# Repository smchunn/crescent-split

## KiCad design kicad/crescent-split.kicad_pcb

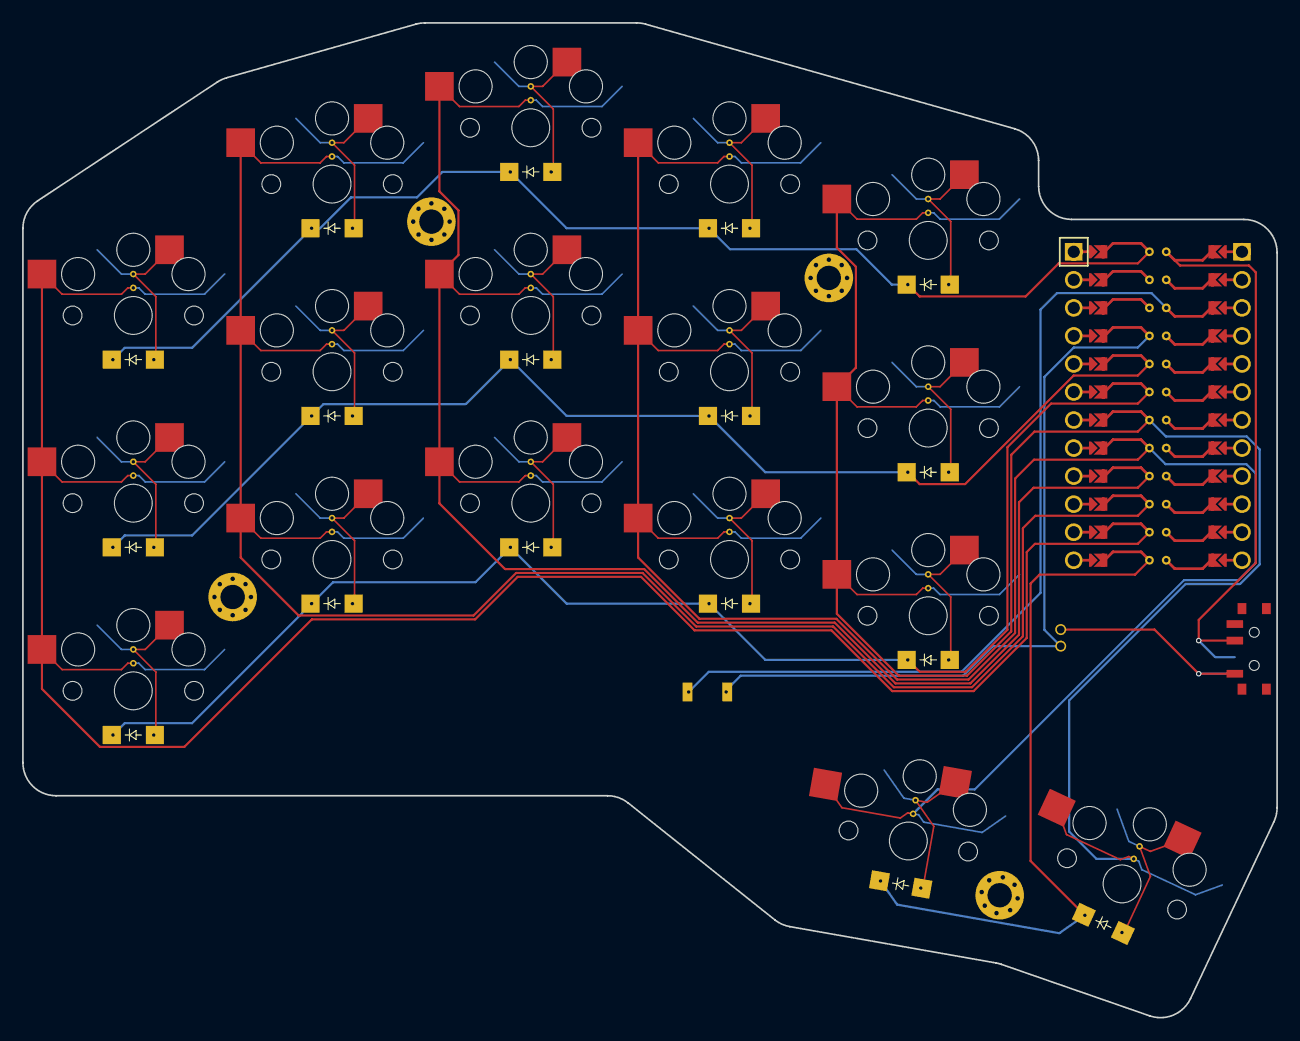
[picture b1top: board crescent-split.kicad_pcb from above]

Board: 2 copper layers, 113.6 x 90.1 mm, 39 parts (0 on the bottom side), 27 nets.

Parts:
D1, D2, D3, D4, D5, D6, D7, D8, D9, D10, D11, D12, D13, D14, D15, D16, D17: ComboDiode
MCU1: ProMicro
S1, S2, S3, S4, S5, S6, S7, S8, S9, S10, S11, S12, S13, S14, S15, S16, S17: PG1350
_38, _39, _40, _41: MountingHole_2.2mm_M2_Pad_Via

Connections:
GND: MCU1.2, MCU1.21, MCU1.22
P1: D3.1, D6.1, D9.1, D12.1, D15.1, MCU1.24
P2: D2.1, D5.1, D8.1, D11.1, D14.1, MCU1.20
P3: D1.1, D4.1, D7.1, D10.1, D13.1, MCU1.19
P4: MCU1.18, S13.2, S14.2, S15.2, S17.2
P5: MCU1.17, S10.2, S11.2, S12.2, S16.2
P6: MCU1.16, S7.2, S8.2, S9.2
P7: MCU1.15, S4.2, S5.2, S6.2
P8: MCU1.14, S1.2, S2.2, S3.2
P9: D16.1, D17.1, MCU1.13
index_bottom: D10.2, S10.1
index_home: D11.2, S11.1
index_thome: D16.2, S16.1
index_top: D12.2, S12.1
inner_bottom: D13.2, S13.1
inner_home: D14.2, S14.1
inner_thome: D17.2, S17.1
inner_top: D15.2, S15.1
middle_bottom: D7.2, S7.1
middle_home: D8.2, S8.1
middle_top: D9.2, S9.1
pinky_bottom: D1.2, S1.1
pinky_home: D2.2, S2.1
pinky_top: D3.2, S3.1
ring_bottom: D4.2, S4.1
ring_home: D5.2, S5.1
ring_top: D6.2, S6.1

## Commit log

2023-05-16 add git ignore
2023-05-16 add footprints
2023-05-16 add ergogen config
2023-05-17 change kicad project name and remove case generation from config
2023-05-19 move to separate ergogen repo
2023-05-19 cleanup
